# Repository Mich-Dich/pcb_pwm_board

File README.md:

# PWM Board v1.0.0 – User Guide

## Overview

The **PWM Board** is a 16‑channel PWM controller board designed for driving servos, LEDs, or small DC motors. It is built around the **PCA9685** 16‑channel 12‑bit PWM driver, controlled by an **STM32L010F4P6** Arm® Cortex®‑M0+ MCU. Communication is via **RS‑485** (using a SP3485 transceiver), making it suitable for remote or industrial applications. The board also features six low‑side N‑MOSFET outputs (with flyback diodes) for higher‑current loads such as motors or solenoids, and a dedicated 3.3 V buck converter (SY81051) that generates the logic supply from a 12 V input.

## Features

- **16 independent PWM channels** (12‑bit resolution) – 10 are brought out to 3‑pin headers (signal, 3.3 V, GND) for servos/LEDs, and 6 drive N‑MOSFETs for higher‑current loads.
- **On‑board STM32L010F4P6 MCU** – handles RS‑485 communication and controls the PCA9685.
- **RS‑485 interface** – half‑duplex, with automatic direction control via the MCU’s `SEND_CTL` signal.
- **Low‑side MOSFET outputs** – six N‑channel MOSFETs (SOT‑23) with flyback diodes (SOD‑523) for driving inductive loads (motors, relays, etc.).
- **On‑board 3.3 V regulator** – SY81051 step‑down converter, capable of delivering up to 1.5 A (depending on input voltage and thermal conditions).
- **Programming & debugging** – standard 5‑pin SWD header (J11) for use with ST‑Link or compatible debuggers.
- **User button** – SW1 (tactile switch) connected to PA6 for custom firmware functions.
- **Power and status LEDs**:
  - Red LED (D1) – 3.3 V power indicator.
  - Red LED (D2) and green LED (D3) – general‑purpose, connected to MCU pins PA3 and PA5.
- **Compact size** – 51 mm × 41 mm.

## Specifications

| Parameter              | Value                            |
|------------------------|----------------------------------|
| Input voltage          | 12 V DC (nominal)                |
| Logic voltage          | 3.3 V (on‑board buck converter)  |
| PWM channels           | 16 (12‑bit PCA9685)              |
| Servo/ LED headers     | 10× 3‑pin (J0–J9)                |
| Motor/ MOSFET outputs  | 6× 2‑pin (J12–J17)               |
| Communication          | RS‑485 (half‑duplex)             |
| MCU                    | STM32L010F4P6 (TSSOP‑20)         |
| Programming interface  | SWD (5‑pin, 2.54 mm pitch)       |
| Board dimensions       | 51 mm × 41 mm                    |
| Mounting holes         | 4× M2 (2.2 mm diameter)          |

## Connectors and Pinout

### Power and RS‑485 – J10 (1×04 pin header)

| Pin | Function      | Description                                 |
|-----|---------------|---------------------------------------------|
| 1   | +12V          | Main power input (12 V DC)                  |
| 2   | GND           | Ground                                      |
| 3   | RS‑485 B      | RS‑485 differential line B (inverting)      |
| 4   | RS‑485 A      | RS‑485 differential line A (non‑inverting)  |

### Servo / LED Headers – J0 to J9 (1×03 pin headers)

| Pin | Function      | Description                                               |
|-----|---------------|-----------------------------------------------------------|
| 1   | GND           | Ground                                                    |
| 2   | +3V3          | 3.3 V logic supply (for servos/LEDs, check current limit) |
| 3   | PWM signal    | PWM output from PCA9685 channel 0‑9                       |

*Note:* The 3.3 V supply on these headers is derived from the on‑board regulator. Total current available for external loads depends on the input voltage and regulator capability (max ~5A). For high‑power servos, use an external servo supply and only connect signal and GND.

### Motor / MOSFET Outputs – J12 to J17 (1×02 pin headers)

| Pin | Function      | Description                         |
|-----|---------------|-------------------------------------|
| 1   | OUTn          | Drain of N‑MOSFET (low‑side switch) |
| 2   | +12V          | 12 V supply (shared with input)     |

Each output uses an N‑MOSFET (Q0–Q5) with the source connected to GND through a flyback diode (D4–D9) to +12V. This configuration is suitable for driving inductive loads (e.g., small DC motors, solenoids) with PWM from the PCA9685. The MOSFETs are controlled by PCA9685 channels 10–15 respectively.

### Programming Header – J11 (1×05 pin header, SWD)

| Pin | Function      | Description                                         |
|-----|---------------|-----------------------------------------------------|
| 1   | GND           | Ground                                              |
| 2   | NRST          | MCU reset (optional for debugging)                  |
| 3   | SWCLK         | SWD clock                                           |
| 4   | SWDIO         | SWD data I/O                                        |
| 5   | +3V3          | 3.3 V output (can be used to power the programmer)  |

### User Button – SW1

Momentary push button connected to MCU pin PA6. Pressing the button pulls the pin high.

### LEDs

- **D1 (red)** – 3.3 V power indicator, connected to the 3.3 V rail.
- **D2 (red)** – connected to MCU PA3 (active high).
- **D3 (green)** – connected to MCU PA5 (active high).

## Power

The board accepts a 12 V DC input on J10. An internal buck converter (U3, SY81051) generates 3.3 V for the logic and for the servo/LED headers. The 3.3 V rail is also available on the SWD header and can be used to power an external programmer if needed.

**Important:** The total current drawn from the 3.3 V rail (including MCU, PCA9685, and any loads on the servo headers) must not exceed the regulator’s capability. Under typical conditions, the SY81051 can deliver up to 5 A, but thermal performance and input voltage will affect the actual limit.

## Programming the STM32

The STM32L010F4P6 can be programmed via the SWD interface using any standard Arm debugger (e.g., ST‑Link, J‑Link). Connect your programmer to J11 as follows:

| J11 pin | Programmer connection |
|---------|------------------------|
| 1       | GND                    |
| 3       | SWCLK                  |
| 4       | SWDIO                  |
| 5       | 3.3 V (optional)       |

Pin 2 (NRST) is not strictly required for programming but can be used if your debugger supports it.

The MCU is pre‑programmed with a bootloader or demo firmware? (If none, the user will need to flash their own firmware). The board provides access to all MCU pins for custom development.

## Getting Started

1. **Connect power** – supply 12 V DC to J10 (pins 1 and 2).
2. **Check the red LED D1** – it should light, indicating 3.3 V is present.
3. **Connect RS‑485** – if used, connect a twisted pair to J10 pins 3 and 4.
4. **Attach loads** – for servos/LEDs, connect to J0–J9; for motors, connect to J12–J17.
5. **Program the MCU** (if needed) via J11.
6. **Communicate** – send commands over RS‑485 to control the PWM outputs. The default communication protocol depends on the firmware loaded. (Refer to the firmware documentation for details.)

## Mechanical Dimensions

- Board outline: 51 mm × 41 mm (rectangular with rounded corners).
- Four M2 mounting holes (2.2 mm diameter) in a cub format fo size: 45x25 mm

## Bill of Materials (BOM)

A detailed BOM in CSV format is provided as `pwm_board.csv`. It includes all components with their values, footprints, and JLCPCB part numbers where available.

## License

This project is licensed under the MIT License. The design files (KiCad) and any accompanying software or firmware are provided under the terms of this license. See the `LICENSE` file for details.

---

**Happy building!** For questions or contributions, please open an issue or pull request in the project repository.

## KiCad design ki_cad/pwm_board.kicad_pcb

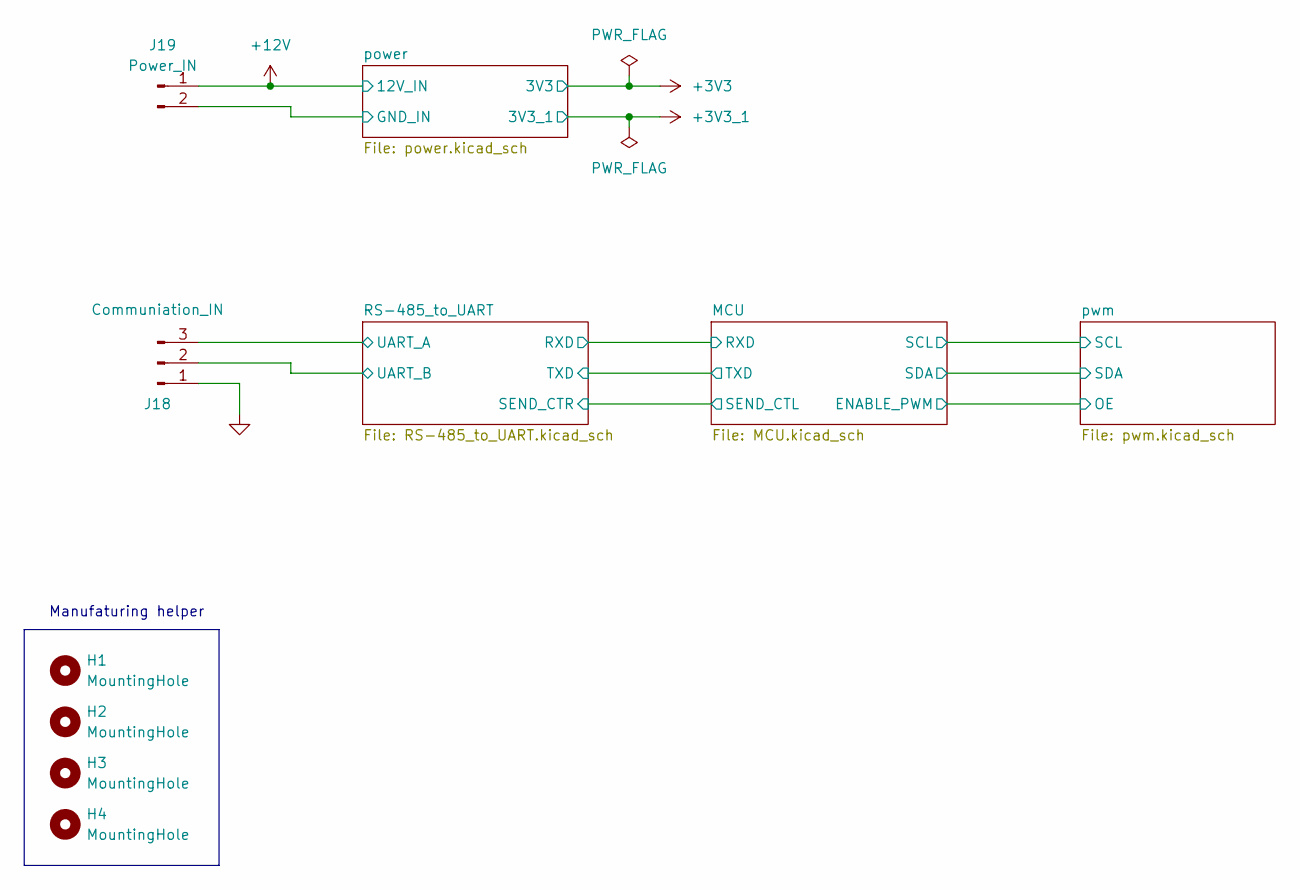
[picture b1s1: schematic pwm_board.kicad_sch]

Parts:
H1, H2, H3, H4: MountingHole; MountingHole_2.2mm_M2
J18: Communiation_IN; PinHeader_1x03_P2.54mm_Vertical; JLCPCB Part # C5383112
J19: Power_IN; TerminalBlock_MaiXu_MX126-5.0-02P_1x02_P5.00mm; JLCPCB Part # C5188434

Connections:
+12V: J19.1; also elsewhere on the board
/RS-485_to_UART/UART_A: J18.3; also elsewhere on the board
/RS-485_to_UART/UART_B: J18.2; also elsewhere on the board
/power/GND_IN: J19.2; also elsewhere on the board
GND: J18.1; also elsewhere on the board

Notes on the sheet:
Manufaturing helper

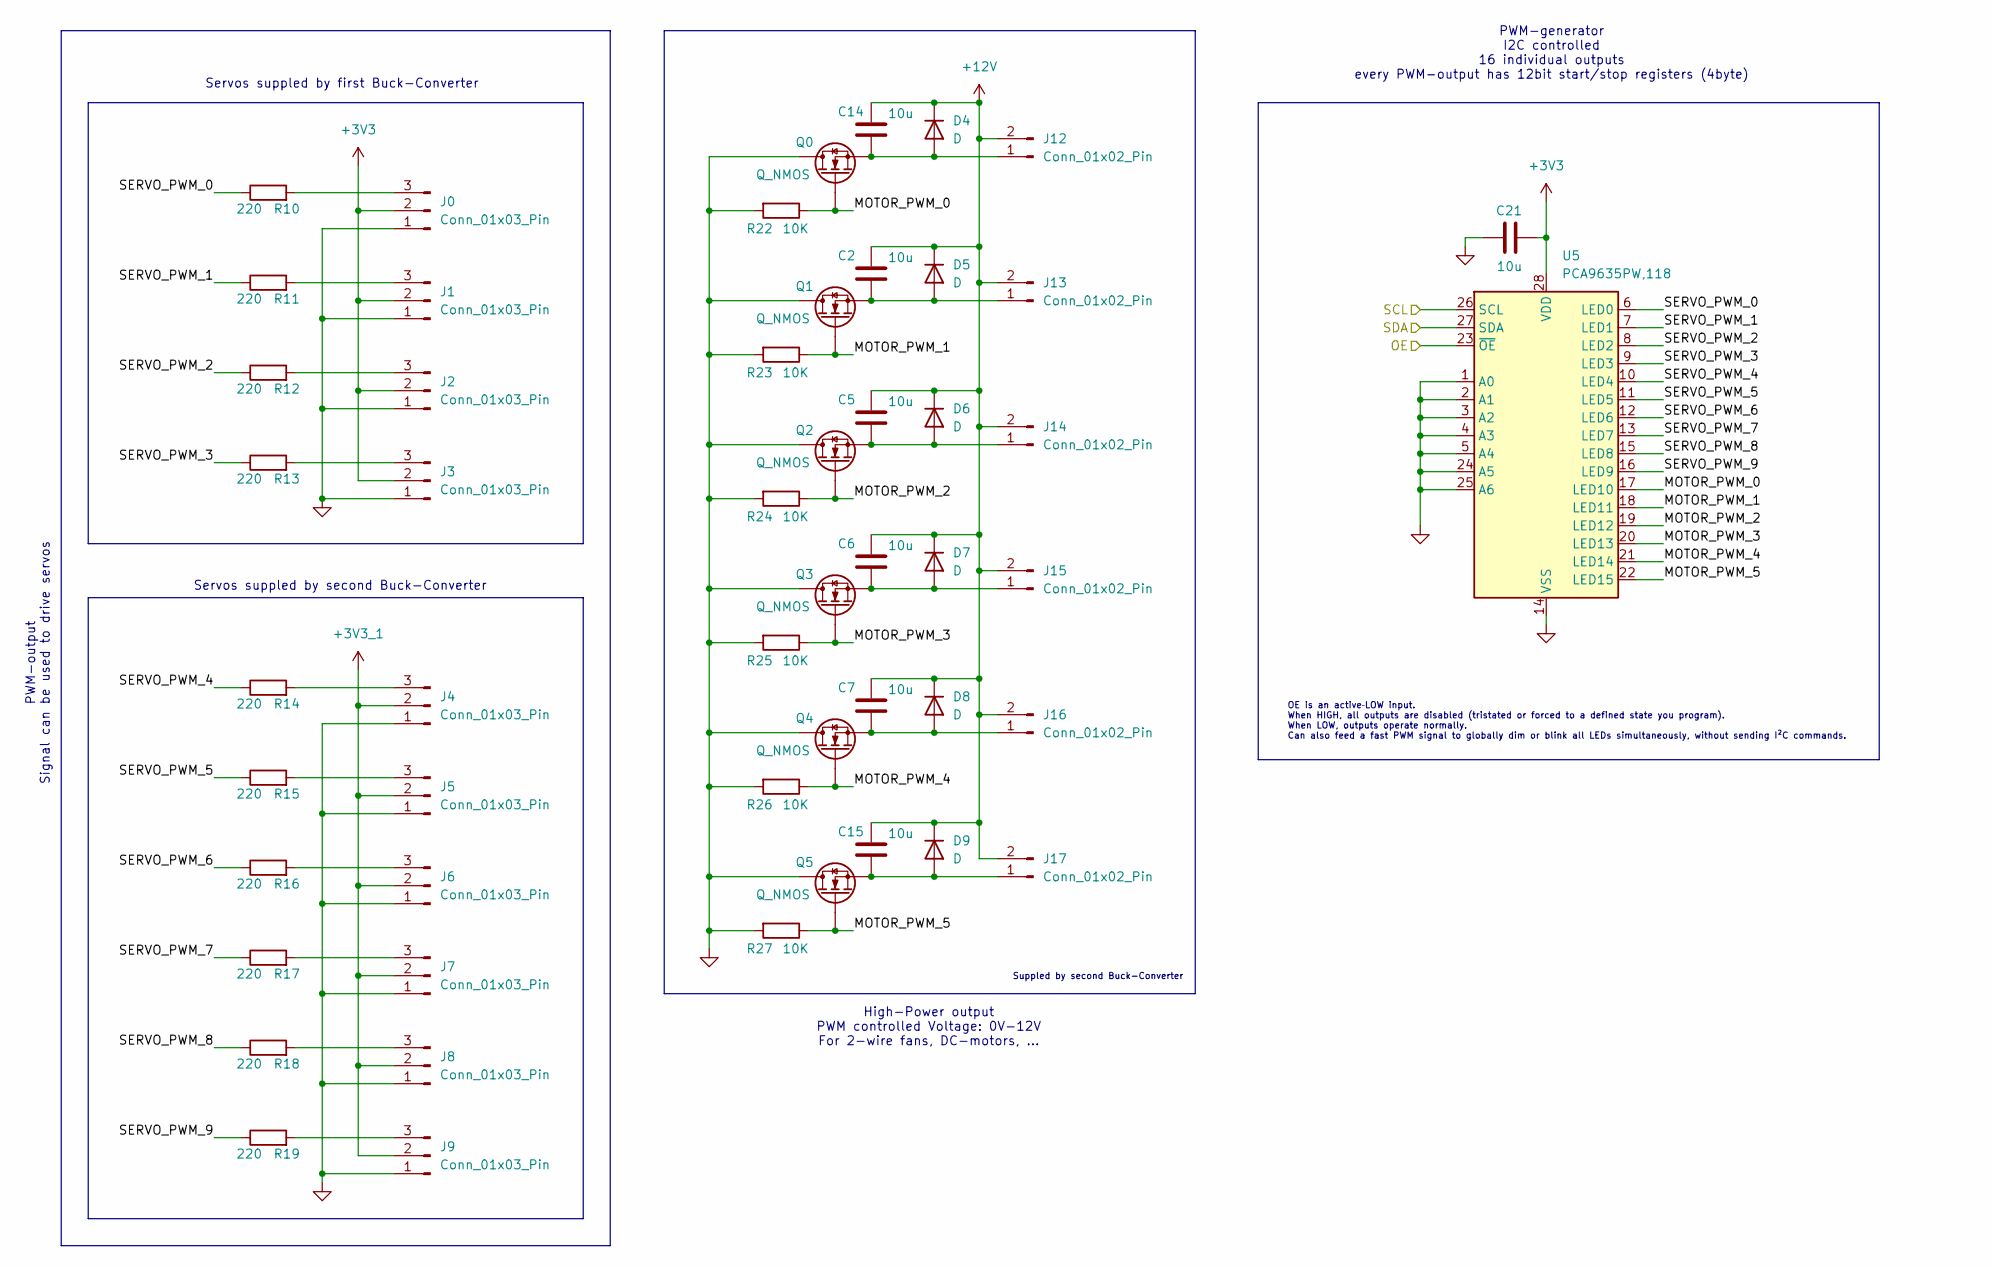
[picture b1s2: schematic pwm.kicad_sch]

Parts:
C2, C5, C6, C7, C14, C15: 10u; C_0603_1608Metric; JLCPCB Part # C96446
C21: 10u; C_0402_1005Metric; JLCPCB Part # C15525
D4, D5, D6, D7, D8, D9: D; D_SOD-323; JLCPCB Part # C5334579
J0, J1, J2, J3, J4, J5, J6, J7, J8, J9: Conn_01x03_Pin; PinHeader_1x03_P2.54mm_Vertical; JLCPCB Part # C5383112
J12, J13, J14, J15, J16, J17: Conn_01x02_Pin; PinHeader_1x02_P2.54mm_Vertical; JLCPCB Part # C5383111
Q0, Q1, Q2, Q3, Q4, Q5: Q_NMOS; SOT-23; JLCPCB Part # C5340723
R10, R11, R12, R13, R14, R15, R16, R17, R18, R19: 220; R_0402_1005Metric; JLCPCB Part # C25091
R22, R23, R24, R25, R26, R27: 10K; R_0805_2012Metric; JLCPCB Part # C17414
U5: PCA9635PW,118; TSSOP-28_4.4x9.7mm_P0.65mm; JLCPCB Part # C110795

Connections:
+3V3: C21.2, J0.2, J1.2, J2.2, J3.2, U5.28 (VDD); also elsewhere on the board
+3V3_1: J4.2, J5.2, J6.2, J7.2, J8.2, J9.2; also elsewhere on the board
+12V: C2.1, C5.1, C6.1, C7.1, C14.1, C15.1, D4.1 (K), D5.1 (K), D6.1 (K), D7.1 (K), D8.1 (K), D9.1 (K), J12.2, J13.2, J14.2, J15.2, J16.2, J17.2; also elsewhere on the board
/MCU/ENABLE_PWM: U5.23 (~OE); also elsewhere on the board
/MCU/SCL: U5.26 (SCL); also elsewhere on the board
/MCU/SDA: U5.27 (SDA); also elsewhere on the board
/pwm/MOTOR_PWM_0: Q0.G, R22.1, U5.17 (LED10)
/pwm/MOTOR_PWM_1: Q1.G, R23.1, U5.18 (LED11)
/pwm/MOTOR_PWM_2: Q2.G, R24.1, U5.19 (LED12)
/pwm/MOTOR_PWM_3: Q3.G, R25.1, U5.20 (LED13)
/pwm/MOTOR_PWM_4: Q4.G, R26.1, U5.21 (LED14)
/pwm/MOTOR_PWM_5: Q5.G, R27.1, U5.22 (LED15)
/pwm/SERVO_PWM_0: R10.1, U5.6 (LED0)
/pwm/SERVO_PWM_1: R11.1, U5.7 (LED1)
/pwm/SERVO_PWM_2: R12.1, U5.8 (LED2)
/pwm/SERVO_PWM_3: R13.1, U5.9 (LED3)
/pwm/SERVO_PWM_4: R14.1, U5.10 (LED4)
/pwm/SERVO_PWM_5: R15.1, U5.11 (LED5)
/pwm/SERVO_PWM_6: R16.1, U5.12 (LED6)
/pwm/SERVO_PWM_7: R17.1, U5.13 (LED7)
/pwm/SERVO_PWM_8: R18.1, U5.15 (LED8)
/pwm/SERVO_PWM_9: R19.1, U5.16 (LED9)
GND: C21.1, J0.1, J1.1, J2.1, J3.1, J4.1, J5.1, J6.1, J7.1, J8.1, J9.1, Q0.D, Q1.D, Q2.D, Q3.D, Q4.D, Q5.D, R22.2, R23.2, R24.2, R25.2, R26.2, R27.2, U5.1 (A0), U5.2 (A1), U5.3 (A2), U5.4 (A3), U5.5 (A4), U5.14 (VSS), U5.24 (A5), U5.25 (A6); also elsewhere on the board
unnamed: C14.2, D4.2 (A), J12.1, Q0.S
unnamed: C2.2, D5.2 (A), J13.1, Q1.S
unnamed: C5.2, D6.2 (A), J14.1, Q2.S
unnamed: C6.2, D7.2 (A), J15.1, Q3.S
unnamed: C7.2, D8.2 (A), J16.1, Q4.S
unnamed: C15.2, D9.2 (A), J17.1, Q5.S
unnamed: J0.3, R10.2
unnamed: J1.3, R11.2
unnamed: J2.3, R12.2
unnamed: J3.3, R13.2
unnamed: J4.3, R14.2
unnamed: J5.3, R15.2
unnamed: J6.3, R16.2
unnamed: J7.3, R17.2
unnamed: J8.3, R18.2
unnamed: J9.3, R19.2

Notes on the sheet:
High-Power output PWM controlled Voltage: 0V-12V For 2-wire fans, DC-motors, ...
Servos suppled by first Buck-Converter
PWM-generator I2C controlled 16 individual outputs every PWM-output has 12bit start/stop registers (4byte)
PWM-output Signal can be used to drive servos
Servos suppled by second Buck-Converter
Suppled by second Buck-Converter
OE is an active‑LOW input. When HIGH, all outputs are disabled (tristated or forced to a defined state you program). When LOW, outputs operate normally. Can also feed a fast PWM signal to globally dim or blink all LEDs simultaneously, without sending I²C commands.

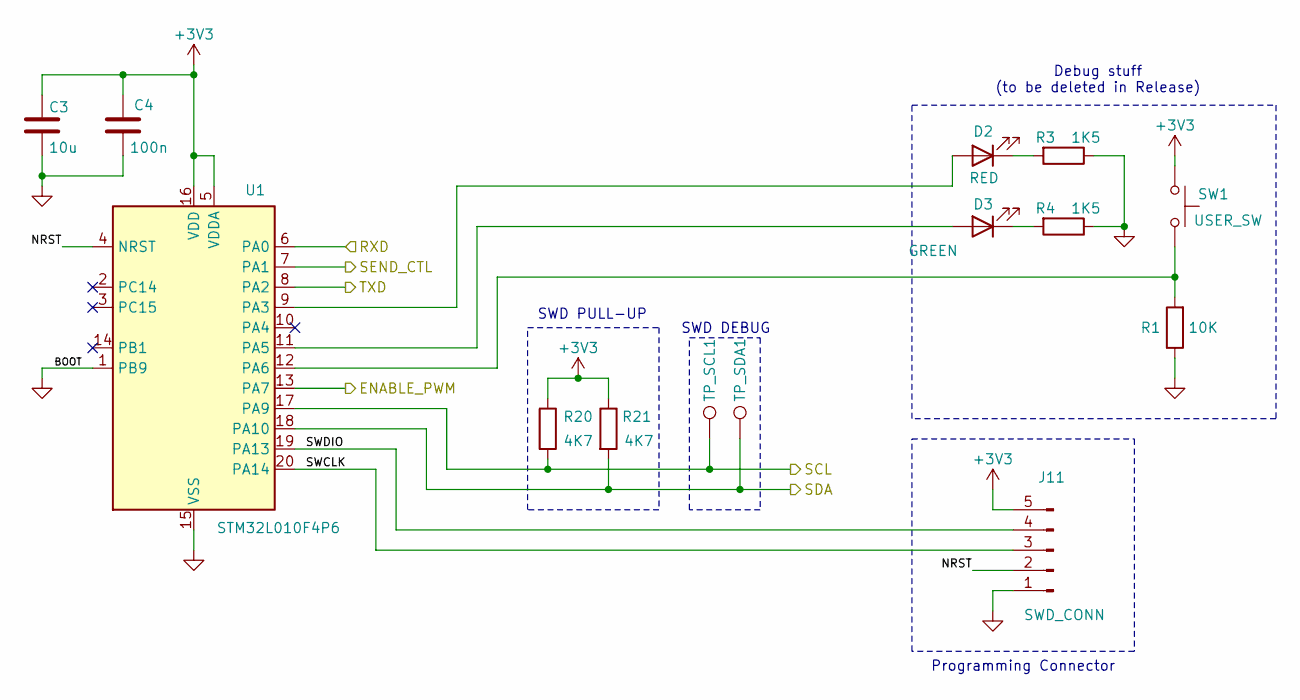
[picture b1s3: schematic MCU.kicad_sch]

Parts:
C3: 10u; C_0402_1005Metric; JLCPCB Part # C15525
C4: 100n; C_0402_1005Metric; JLCPCB Part # C307331
D2: RED; LED_0603_1608Metric; JLCPCB Part # C2286
D3: GREEN; LED_0603_1608Metric; JLCPCB Part # C2290
J11: SWD_CONN; PinHeader_1x05_P2.54mm_Vertical; JLCPCB Part # C5383114
R1: 10K; R_0805_2012Metric; JLCPCB Part # C17414
R3, R4: 1K5; R_0402_1005Metric; JLCPCB Part # C25867
R20, R21: 4K7; R_0402_1005Metric; JLCPCB Part # C25900
SW1: USER_SW; SW_PUSH_TS-1088-AR02016; JLCPCB Part # C720477
TP_SCL1: TestPoint; TestPoint_Pad_D1.5mm
TP_SDA1: TestPoint; TestPoint_Pad_D1.5mm
U1: STM32L010F4P6; TSSOP-20_4.4x6.5mm_P0.65mm; JLCPCB Part # C529415

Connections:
+3V3: C3.1, C4.2, J11.5, R20.1, R21.1, SW1.1, U1.5 (VDDA), U1.16 (VDD); also elsewhere on the board
/MCU/ENABLE_PWM: U1.13 (PA7); also elsewhere on the board
/MCU/NRST: J11.2, U1.4 (NRST)
/MCU/RXD: U1.6 (PA0); also elsewhere on the board
/MCU/SCL: R20.2, TP_SCL1.1, U1.17 (PA9); also elsewhere on the board
/MCU/SDA: R21.2, TP_SDA1.1, U1.18 (PA10); also elsewhere on the board
/MCU/SEND_CTL: U1.7 (PA1); also elsewhere on the board
/MCU/SWCLK: J11.3, U1.20 (PA14)
/MCU/SWDIO: J11.4, U1.19 (PA13)
/MCU/TXD: U1.8 (PA2); also elsewhere on the board
GND: C3.2, C4.1, J11.1, R1.1, R3.1, R4.1, U1.1 (PB9), U1.15 (VSS); also elsewhere on the board
unnamed: D2.2 (A), U1.9 (PA3)
unnamed: D2.1 (K), R3.2
unnamed: D3.2 (A), U1.11 (PA5)
unnamed: D3.1 (K), R4.2
unnamed: R1.2, SW1.2, U1.12 (PA6)

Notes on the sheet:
SWD DEBUG
SWD PULL-UP
Programming Connector
Debug stuff (to be deleted in Release)

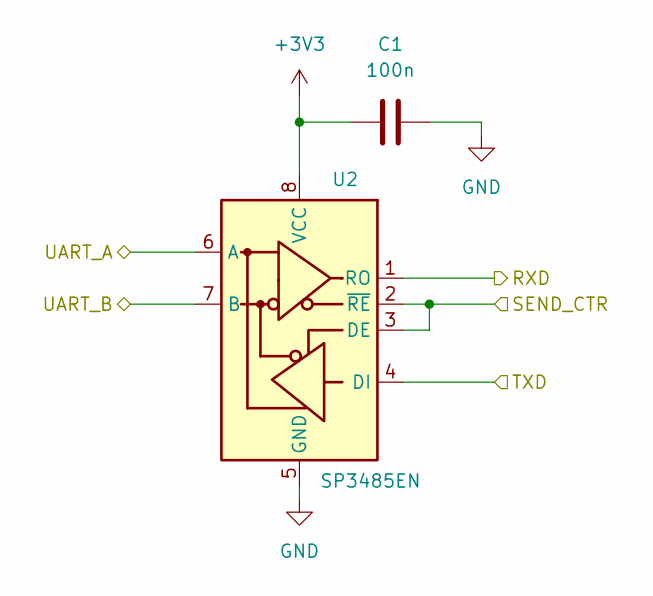
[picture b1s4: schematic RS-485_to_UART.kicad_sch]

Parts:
C1: 100n; C_0402_1005Metric; JLCPCB Part # C307331
U2: SP3485EN; SOIC-8_3.9x4.9mm_P1.27mm; JLCPCB Part # C8963

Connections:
+3V3: C1.1, U2.8 (VCC); also elsewhere on the board
/MCU/RXD: U2.1 (RO); also elsewhere on the board
/MCU/SEND_CTL: U2.2 (~RE), U2.3 (DE); also elsewhere on the board
/MCU/TXD: U2.4 (DI); also elsewhere on the board
/RS-485_to_UART/UART_A: U2.6 (A); also elsewhere on the board
/RS-485_to_UART/UART_B: U2.7 (B); also elsewhere on the board
GND: C1.2, U2.5 (GND); also elsewhere on the board

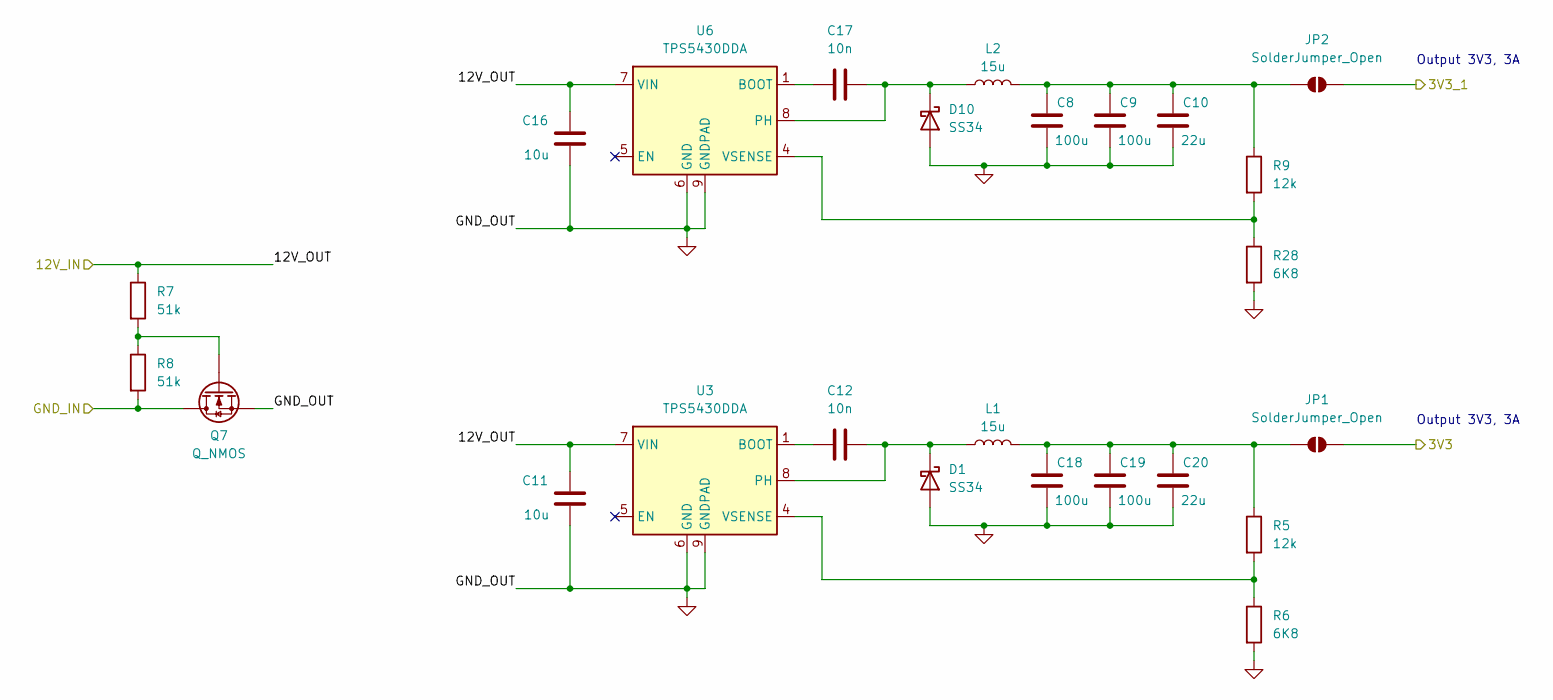
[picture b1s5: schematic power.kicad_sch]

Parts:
C8, C9, C18, C19: 100u; C_1206_3216Metric; JLCPCB Part # C15008
C10, C20: 22u; C_0805_2012Metric; JLCPCB Part # C45783
C11, C16: 10u; C_0805_2012Metric; JLCPCB Part # C15850
C12, C17: 10n; C_0805_2012Metric; JLCPCB Part # C1710
D1, D10: SS34; D_SMA; JLCPCB Part # C8678
JP1, JP2: SolderJumper_Open; SolderJumper-2_P1.3mm_Open_TrianglePad1.0x1.5mm
L1, L2: 15u; CYA0630; JLCPCB Part # C5189959
Q7: Q_NMOS; SOT-23-3; JLCPCB Part # C20917
R5, R9: 12k; R_0603_1608Metric; JLCPCB Part # C22790
R6, R28: 6K8; R_0603_1608Metric; JLCPCB Part # C23212
R7, R8: 51k; R_0603_1608Metric; JLCPCB Part # C23196
U3, U6: TPS5430DDA; TI_SO-PowerPAD-8_ThermalVias; JLCPCB Part # C9864

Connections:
+3V3: JP1.2 (B); also elsewhere on the board
+3V3_1: JP2.2 (B); also elsewhere on the board
+12V: C11.1, C16.1, R7.1, U3.7 (VIN), U6.7 (VIN); also elsewhere on the board
/power/GND_IN: Q7.D, R8.2; also elsewhere on the board
GND: C8.2, C9.2, C10.2, C11.2, C16.2, C18.2, C19.2, C20.2, D1.2 (A), D10.2 (A), Q7.S, R6.2, R28.2, U3.6 (GND), U3.9 (GNDPAD), U6.6 (GND), U6.9 (GNDPAD); also elsewhere on the board
unnamed: C12.2, D1.1 (K), L1.1, U3.8 (PH)
unnamed: C17.2, D10.1 (K), L2.1, U6.8 (PH)
unnamed: C18.1, C19.1, C20.1, JP1.1 (A), L1.2, R5.1
unnamed: C8.1, C9.1, C10.1, JP2.1 (A), L2.2, R9.1
unnamed: Q7.G, R7.2, R8.1
unnamed: C12.1, U3.1 (BOOT)
unnamed: R5.2, R6.1, U3.4 (VSENSE)
unnamed: C17.1, U6.1 (BOOT)
unnamed: R9.2, R28.1, U6.4 (VSENSE)

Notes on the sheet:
Output 3V3, 3A

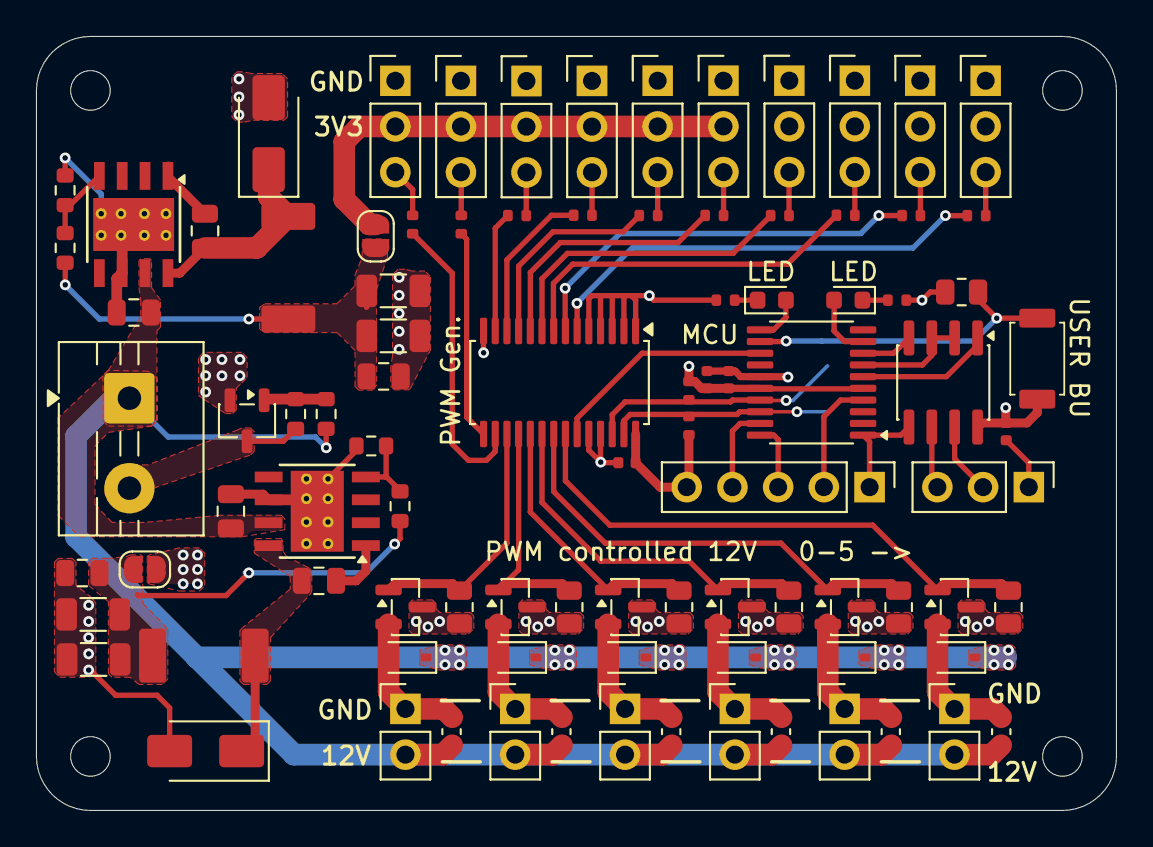
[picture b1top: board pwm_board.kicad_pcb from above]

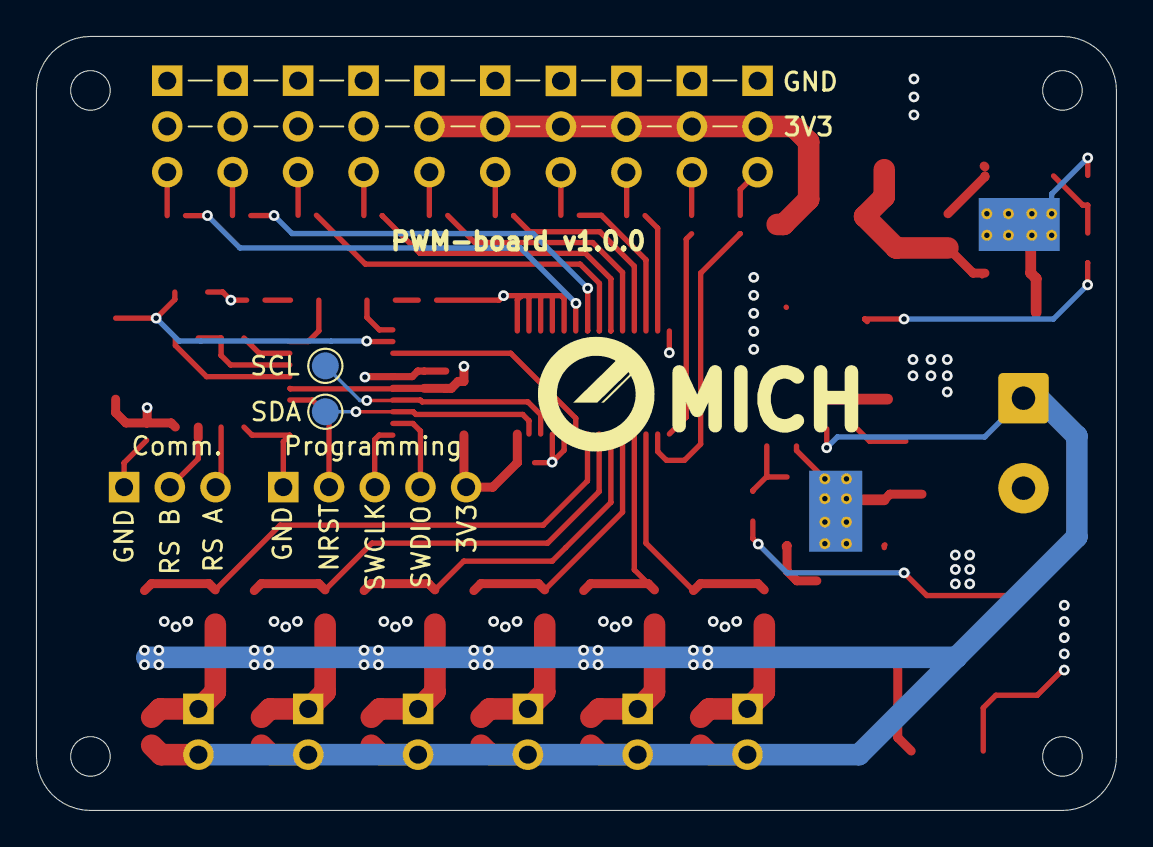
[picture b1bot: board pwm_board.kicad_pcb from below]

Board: 4 copper layers, 60.0 x 43.0 mm, 99 parts (2 on the bottom side), 62 nets.

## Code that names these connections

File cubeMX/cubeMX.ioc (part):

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Mcu.Name=STM32L010F4Px
Mcu.Package=TSSOP20
Mcu.UserName=STM32L010F4Px
PA0-CK_IN.Mode=Asynchronous
PA0-CK_IN.Signal=USART2_RX
PA10.Mode=I2C
PA10.Signal=I2C1_SDA
PA13.Mode=Serial_Wire
PA13.Signal=SYS_SWDIO
PA14.Mode=Serial_Wire
PA14.Signal=SYS_SWCLK
PA2.Mode=Asynchronous
PA2.Signal=USART2_TX
PA3.Signal=S_TIM21_CH2
PA5.Signal=S_TIM2_CH1
PA9.Mode=I2C
PA9.Signal=I2C1_SCL
RCC.HSE_VALUE=8000000
RCC.SYSCLKFreq_VALUE=2097000
board=custom

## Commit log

2026-03-01 semi finished
2026-03-04 update after feedback (purchased)
2026-03-19 update parts && add test points
2026-03-22 create CubeMX project && start programming
2026-03-26 enable debugging from VSCode with step through and breakpoints
2026-03-30 update code
2026-04-13 copy arduino lib for PCA9635
